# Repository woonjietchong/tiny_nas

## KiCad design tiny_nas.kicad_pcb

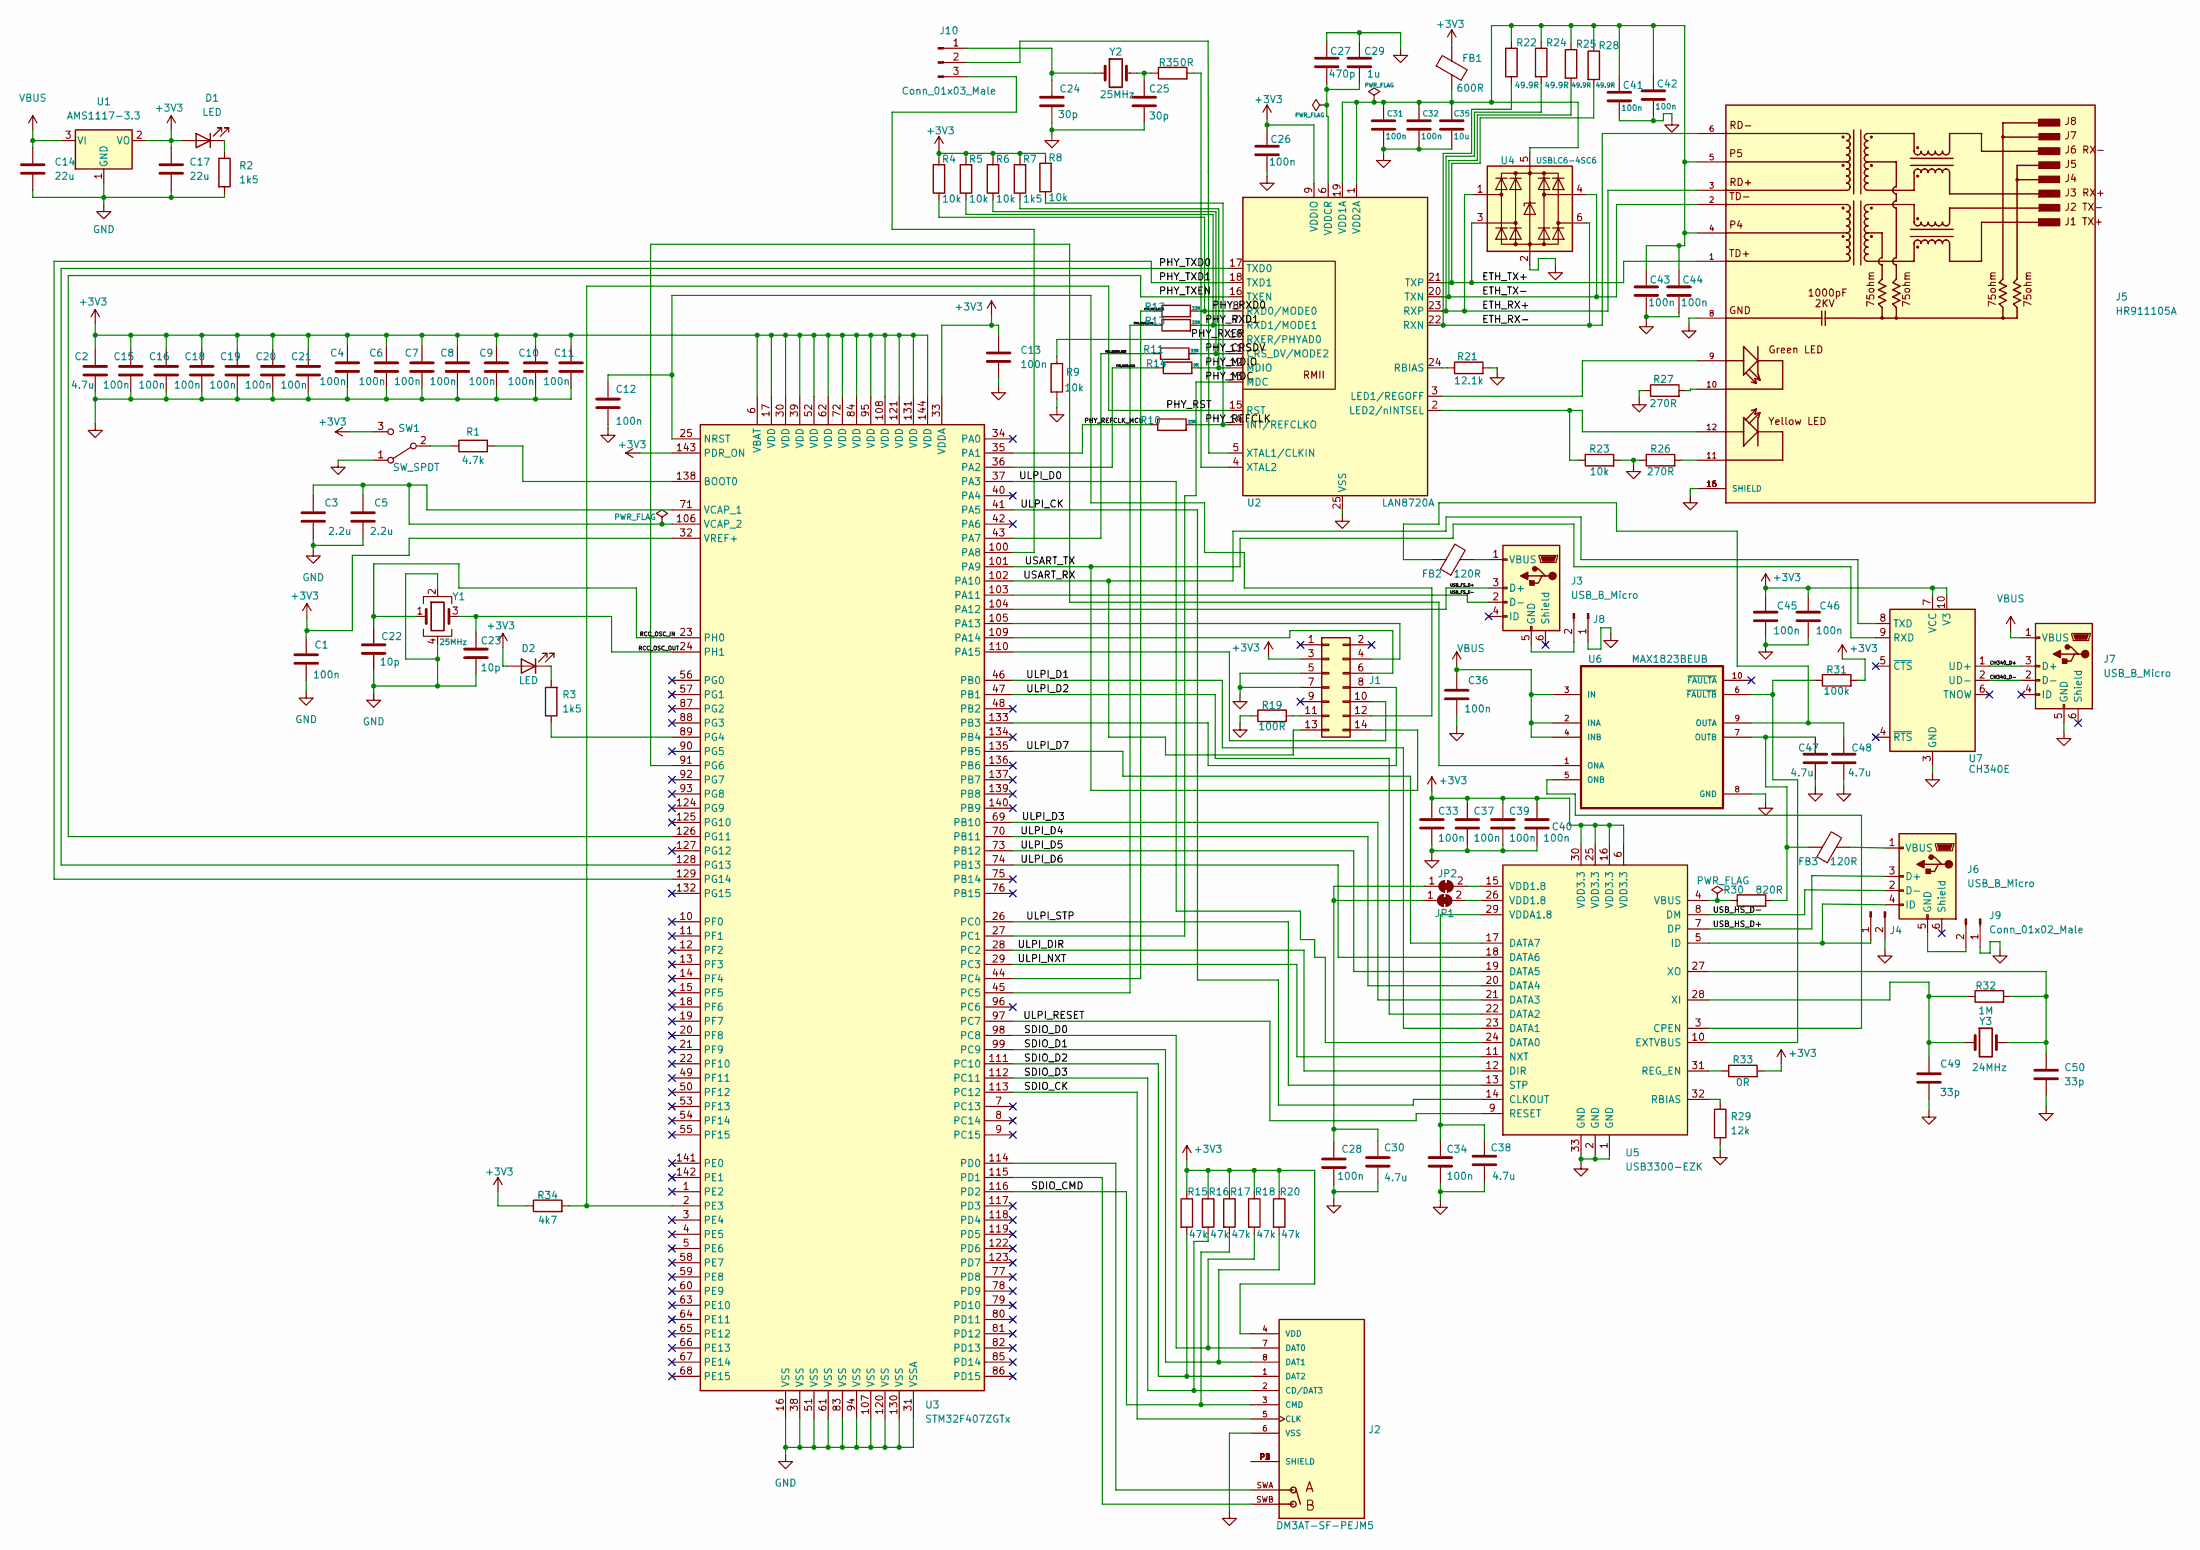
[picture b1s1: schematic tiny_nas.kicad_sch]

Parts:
C1, C4, C6, C7, C8, C9, C10, C11, C12, C13, C15, C16, C18, C19, C20, C21, C26, C28, C31, C32, C33, C34, C36, C37, C39, C40, C41, C42, C43, C44, C45, C46: 100n; C_0402_1005Metric
C2, C30, C38, C47, C48: 4.7u; C_0603_1608Metric
C3, C5: 2.2u; C_0603_1608Metric
C14, C17: 22u; C_0805_2012Metric
C22, C23: 10p; C_0402_1005Metric
C24, C25: 30p; C_0402_1005Metric
C27: 470p; C_0402_1005Metric
C29: 1u; C_0603_1608Metric
C35: 10u; C_0805_2012Metric
C49, C50: 33p; C_0402_1005Metric
D1, D2: LED; LED_0603_1608Metric
FB1: 600R; L_0603_1608Metric
FB2, FB3: 120R; L_0603_1608Metric
J1: Conn_02x07_Odd_Even; PinHeader_2x07_P1.27mm_Vertical
J2: DM3AT-SF-PEJM5; HRS_DM3AT-SF-PEJM5
J3, J6, J7: USB_B_Micro; USB_Micro-B_Molex_47346-0001
J4, J8, J9: Conn_01x02_Male; PinHeader_1x02_P2.54mm_Vertical
J5: HR911105A; HANRUN_HR911105A; PARTREV A
J10: Conn_01x03_Male; PinHeader_1x03_P2.54mm_Vertical
JP1, JP2: SolderJumper_2_Bridged; SolderJumper-2_P1.3mm_Bridged_RoundedPad1.0x1.5mm
R1: 4.7k; R_0402_1005Metric
R2, R3, R7: 1k5; R_0402_1005Metric
R4, R5, R6, R8, R9, R23: 10k; R_0402_1005Metric
R10, R11, R12, R13: 33R; R_0402_1005Metric
R14, R33, R35: 0R; R_0603_1608Metric
R15, R16, R17, R18, R20: 47k; R_0402_1005Metric
R19: 100R; R_0402_1005Metric
R21: 12.1k; R_0402_1005Metric
R22, R24, R25, R28: 49.9R; R_0805_2012Metric
R26, R27: 270R; R_0603_1608Metric
R29: 12k; R_0402_1005Metric
R30: 820R; R_0603_1608Metric
R31: 100k; R_0402_1005Metric
R32: 1M; R_0402_1005Metric
R34: 4k7; R_0402_1005Metric
SW1: SW_SPDT; SW_SPDT_PCM12
U1: AMS1117-3.3; SOT-223-3_TabPin2
U2: LAN8720A; QFN-24-1EP_4x4mm_P0.5mm_EP2.6x2.6mm
U3: STM32F407ZGTx; LQFP-144_20x20mm_P0.5mm
U4: USBLC6-4SC6; SOT-23-6
U5: USB3300-EZK; QFN-32-1EP_5x5mm_P0.5mm_EP3.45x3.45mm
U6: MAX1823BEUB; SOP50P490X110-10N
U7: CH340E; MSOP-10_3x3mm_P0.5mm
Y1: 25MHz; Crystal_SMD_3225-4Pin_3.2x2.5mm
Y2: 25MHz; Crystal_HC49-U_Vertical
Y3: 24MHz; Crystal_HC49-U_Vertical

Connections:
+3V3: C1.1, C2.1, C4.1, C6.1, C7.1, C8.1, C9.1, C10.1, C11.1, C13.1, C15.1, C16.1, C17.1, C18.1, C19.1, C20.1, C21.1, C26.1, C33.1, C37.1, C39.1, C40.1, C45.1, C46.1, D1.2 (A), D2.2 (A), FB1.1, J1.3, J2.4 (VDD), R4.2, R5.2, R6.2, R7.2, R8.2, R15.1, R16.1, R17.1, R18.1, R20.1, R31.2, R33.2, R34.1, SW1.3 (C), U1.2 (VO), U2.9 (VDDIO), U3.6 (VBAT), U3.17 (VDD), U3.30 (VDD), U3.32 (VREF+), U3.33 (VDDA), U3.39 (VDD), U3.52 (VDD), U3.62 (VDD), U3.72 (VDD), U3.84 (VDD), U3.95 (VDD), U3.108 (VDD), U3.121 (VDD), U3.131 (VDD), U3.143 (PDR_ON), U3.144 (VDD), U5.6 (VDD3.3), U5.16 (VDD3.3), U5.25 (VDD3.3), U5.30 (VDD3.3), U7.7 (VCC), U7.10 (V3)
/CH340_D+: J7.3 (D+), U7.1 (UD+)
/CH340_D-: J7.2 (D-), U7.2 (UD-)
/ETH_RX+: J5.3, R24.2, U2.23 (RXP), U4.1 (I/O1)
/ETH_RX-: J5.6, R22.2, U2.22 (RXN), U4.6 (I/O4)
/ETH_TX+: J5.1, R28.2, U2.21 (TXP), U4.3 (I/O2)
/ETH_TX-: J5.2, R25.2, U2.20 (TXN), U4.4 (I/O3)
/PHY_CRSDV: R6.1, R11.2, U2.11 (CRS_DV/MODE2)
/PHY_CRSDV_MCU: R11.1, U3.43 (PA7)
/PHY_MDC: U2.13 (MDC), U3.27 (PC1)
/PHY_MDIO: R7.1, R14.2, U2.12 (MDIO)
/PHY_MDIO_MCU: R14.1, U3.36 (PA2)
/PHY_REFCLK: R8.1, R10.2, U2.14 (INT/REFCLKO)
/PHY_REFCLK_MCU: R10.1, U3.35 (PA1)
/PHY_RST: R34.2, U2.15 (RST), U3.2 (PE3)
/PHY_RXD0: R4.1, R12.2, U2.8 (RXD0/MODE0)
/PHY_RXD0_MCU: R12.1, U3.44 (PC4)
/PHY_RXD1: R5.1, R13.2, U2.7 (RXD1/MODE1)
/PHY_RXD1_MCU: R13.1, U3.45 (PC5)
/PHY_RXER: R9.1, U2.10 (RXER/PHYAD0)
/PHY_TXD0: U2.17 (TXD0), U3.128 (PG13)
/PHY_TXD1: U2.18 (TXD1), U3.129 (PG14)
/PHY_TXEN: U2.16 (TXEN), U3.126 (PG11)
/RCC_OSC_IN: C22.1, U3.23 (PH0), Y1.1
/RCC_OSC_OUT: C23.1, U3.24 (PH1), Y1.3
/SDIO_CK: J2.5 (CLK), U3.113 (PC12)
/SDIO_CMD: J2.3 (CMD), R17.2, U3.116 (PD2)
/SDIO_D0: J2.7 (DAT0), R18.2, U3.98 (PC8)
/SDIO_D1: J2.8 (DAT1), R20.2, U3.99 (PC9)
/SDIO_D2: J2.1 (DAT2), R15.2, U3.111 (PC10)
/SDIO_D3: J2.2 (CD/DAT3), R16.2, U3.112 (PC11)
/ULPI_CK: U3.41 (PA5), U5.14 (CLKOUT)
/ULPI_D0: U3.37 (PA3), U5.24 (DATA0)
/ULPI_D1: U3.46 (PB0), U5.23 (DATA1)
/ULPI_D2: U3.47 (PB1), U5.22 (DATA2)
/ULPI_D3: U3.69 (PB10), U5.21 (DATA3)
/ULPI_D4: U3.70 (PB11), U5.20 (DATA4)
/ULPI_D5: U3.73 (PB12), U5.19 (DATA5)
/ULPI_D6: U3.74 (PB13), U5.18 (DATA6)
/ULPI_D7: U3.135 (PB5), U5.17 (DATA7)
/ULPI_DIR: U3.28 (PC2), U5.12 (DIR)
/ULPI_NXT: U3.29 (PC3), U5.11 (NXT)
/ULPI_RESET: U3.97 (PC7), U5.9 (RESET)
/ULPI_STP: U3.26 (PC0), U5.13 (STP)
/USART_RX: J1.13, U3.102 (PA10), U7.8 (TXD)
/USART_TX: J1.14, U3.101 (PA9), U7.9 (RXD)
/USB_FS_D+: J3.3 (D+), U3.104 (PA12)
/USB_FS_D-: J3.2 (D-), U3.103 (PA11)
/USB_HS_D+: J6.3 (D+), U5.7 (DP)
/USB_HS_D-: J6.2 (D-), U5.8 (DM)
GND: C1.2, C2.2, C3.2, C4.2, C5.2, C6.2, C7.2, C8.2, C9.2, C10.2, C11.2, C12.1, C13.2, C14.2, C15.2, C16.2, C17.2, C18.2, C19.2, C20.2, C21.2, C22.2, C23.2, C24.2, C25.2, C26.2, C27.1, C28.2, C29.1, C30.2, C31.2, C32.2, C33.2, C34.2, C35.2, C36.2, C37.2, C38.2, C39.2, C40.2, C41.2, C42.2, C43.2, C44.2, C45.2, C46.2, C47.2, C48.2, C49.2, C50.2, J1.5, J1.7, J2.6 (VSS), J4.2, J5.8, J5.15 (SHIELD), J5.16 (SHIELD), J7.5 (GND), J8.1, J9.1, R2.2, R9.2, R19.1, R21.2, R23.2, R26.1, R27.1, R29.2, SW1.1 (A), U1.1 (GND), U2.25 (VSS), U3.16 (VSS), U3.31 (VSSA), U3.38 (VSS), U3.51 (VSS), U3.61 (VSS), U3.83 (VSS), U3.94 (VSS), U3.107 (VSS), U3.120 (VSS), U3.130 (VSS), U4.2 (GND), U5.1 (GND), U5.2 (GND), U5.33 (GND), U6.8 (GND), U7.3 (GND), Y1.2, Y1.4
unnamed: C3.1, C5.1, U3.71 (VCAP_1), U3.106 (VCAP_2)
unnamed: C12.2, J1.12, U3.25 (NRST)
unnamed: C24.1, J10.1, Y2.1
unnamed: C25.1, R35.1, Y2.2
unnamed: C27.2, C29.2, U2.6 (VDDCR)
unnamed: C28.1, C30.1, JP1.1 (A), JP2.1 (A)
unnamed: C31.1, C32.1, C35.1, C41.1, C42.1, C43.1, C44.1, FB1.2, J5.4, J5.5, R22.1, R24.1, R25.1, R28.1, U2.1 (VDD2A), U2.19 (VDD1A), U4.5 (VBUS)
unnamed: C34.1, C38.1, U5.29 (VDDA1.8)
unnamed: C47.1, FB3.1, R30.2, U6.7 (OUTB)
unnamed: C48.1, FB2.1, U6.9 (OUTA)
unnamed: C49.1, R32.1, U5.28 (XI), Y3.1
unnamed: C50.1, R32.2, U5.27 (XO), Y3.2
unnamed: D1.1 (K), R2.1
unnamed: D2.1 (K), R3.2
unnamed: FB2.2, J3.1 (VBUS)
unnamed: FB3.2, J6.1 (VBUS)
unnamed: J1.4, U3.105 (PA13)
unnamed: J1.6, U3.109 (PA14)
unnamed: J1.8, U3.133 (PB3)
unnamed: J1.10, U3.110 (PA15)
unnamed: J1.11, R19.2
unnamed: J2.P1 (SHIELD), J2.P2 (SHIELD), J2.P3 (SHIELD), J2.P4 (SHIELD)
unnamed: J2.SWA, U3.114 (PD0)
unnamed: J2.SWB, U3.115 (PD1)
unnamed: J3.5 (GND), J8.2
unnamed: J4.1, J6.4 (ID), U5.5 (ID)
unnamed: J5.9, U2.3 (LED1/REGOFF)
unnamed: J5.10, R27.2
unnamed: J5.11, R26.2
unnamed: J5.12, R23.1, U2.2 (LED2/nINTSEL)
unnamed: J6.5 (GND), J9.2
unnamed: J10.2, U2.5 (XTAL1/CLKIN)
unnamed: J10.3, U3.100 (PA8)
unnamed: JP1.2 (B), U5.26 (VDD1.8)
unnamed: JP2.2 (B), U5.15 (VDD1.8)
unnamed: R1.1, SW1.2 (B)
unnamed: R1.2, U3.138 (BOOT0)
unnamed: R3.1, U3.89 (PG4)
unnamed: R21.1, U2.24 (RBIAS)
unnamed: R29.1, U5.32 (RBIAS)
unnamed: R30.1, U5.4 (VBUS)
unnamed: R31.1, U5.10 (EXTVBUS), U6.6 (~FAULTB)
unnamed: R33.1, U5.31 (REG_EN)
unnamed: R35.2, U2.4 (XTAL2)
unnamed: U3.91 (PG6), U6.1 (ONA)
unnamed: U5.3 (CPEN), U6.5 (ONB)
VBUS: C14.1, C36.1, J7.1 (VBUS), U1.3 (VI), U6.2 (INA), U6.3 (IN), U6.4 (INB)

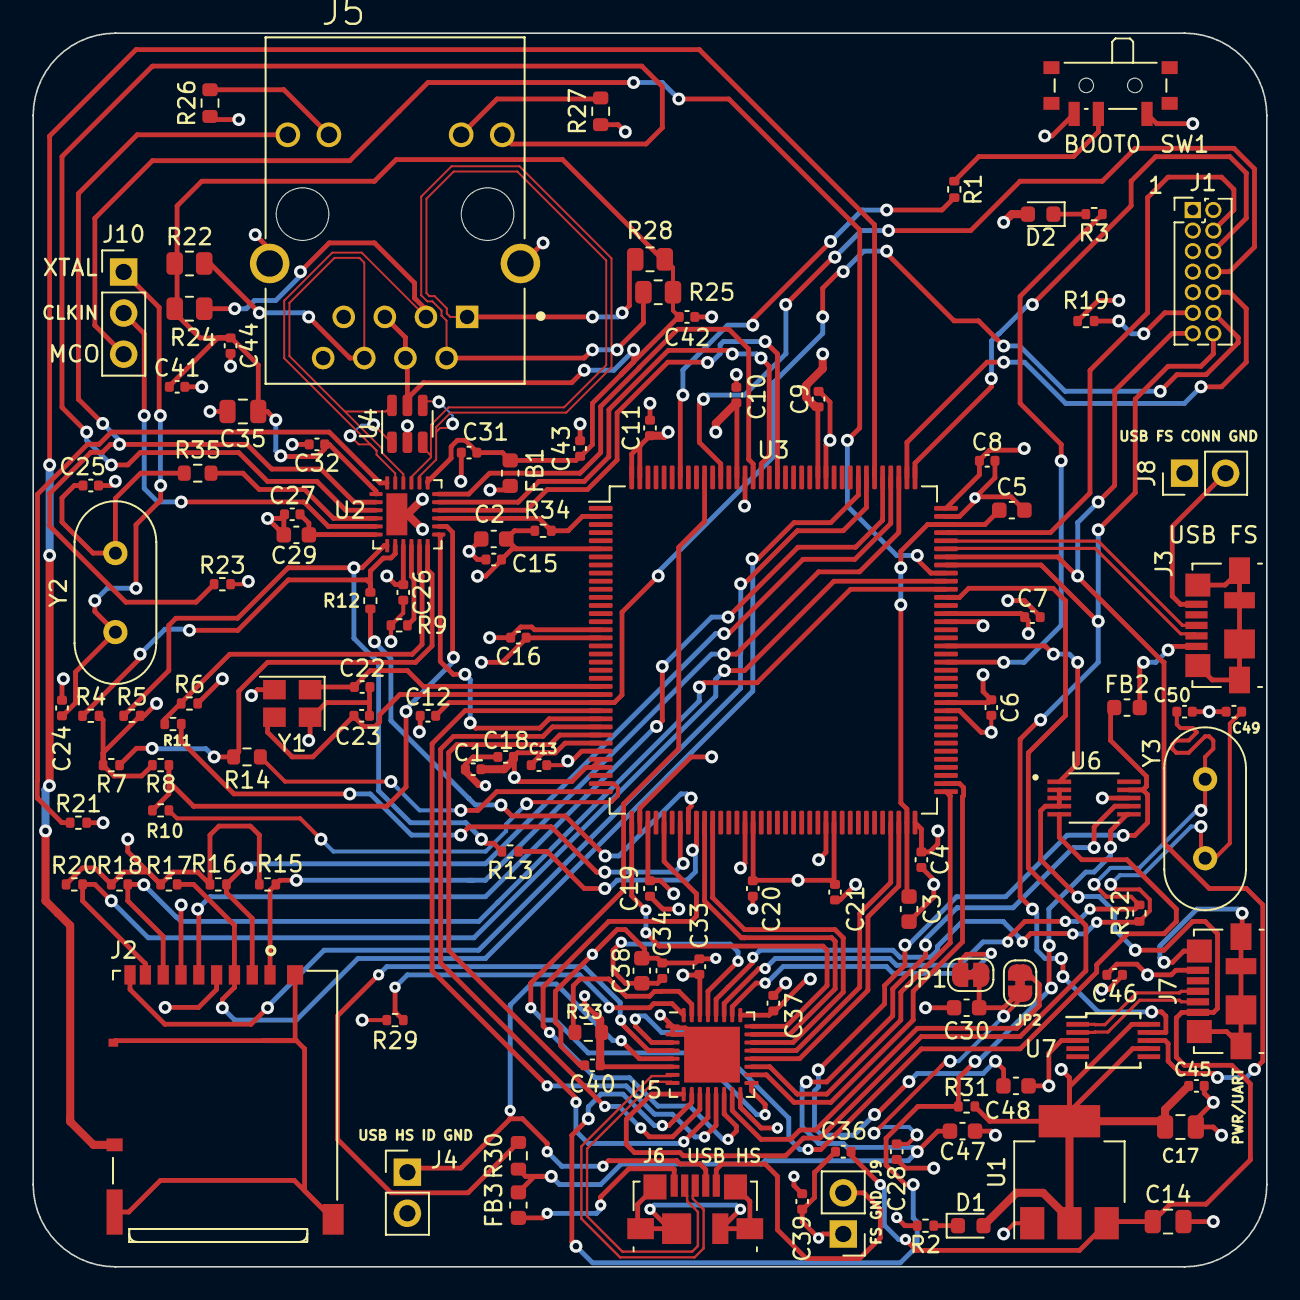
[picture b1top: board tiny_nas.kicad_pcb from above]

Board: 4 copper layers, 76.2 x 76.2 mm, 113 parts (0 on the bottom side), 98 nets.

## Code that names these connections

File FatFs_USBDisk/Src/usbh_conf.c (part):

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	__HAL_RCC_GPIOA_CLK_ENABLE();
	__HAL_RCC_GPIOB_CLK_ENABLE();
	/**USB_OTG_HS GPIO Configuration
	PC0     ------> USB_OTG_HS_ULPI_STP
	PC2     ------> USB_OTG_HS_ULPI_DIR
	PC3     ------> USB_OTG_HS_ULPI_NXT
	PA3     ------> USB_OTG_HS_ULPI_D0
	PA5     ------> USB_OTG_HS_ULPI_CK
	PB0     ------> USB_OTG_HS_ULPI_D1
	PB1     ------> USB_OTG_HS_ULPI_D2
	PB10     ------> USB_OTG_HS_ULPI_D3
	PB11     ------> USB_OTG_HS_ULPI_D4
	PB12     ------> USB_OTG_HS_ULPI_D5
	PB13     ------> USB_OTG_HS_ULPI_D6
	PB5     ------> USB_OTG_HS_ULPI_D7
	*/
	GPIO_InitStruct.Pin = GPIO_PIN_0|GPIO_PIN_2|GPIO_PIN_3;
	GPIO_InitStruct.Mode = GPIO_MODE_AF_PP;
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
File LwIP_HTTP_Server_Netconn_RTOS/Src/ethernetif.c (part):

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  __HAL_RCC_GPIOA_CLK_ENABLE();
  __HAL_RCC_GPIOG_CLK_ENABLE();
  /**ETH GPIO Configuration
  PC1     ------> ETH_MDC
  PA1     ------> ETH_REF_CLK
  PA2     ------> ETH_MDIO
  PA7     ------> ETH_CRS_DV
  PC4     ------> ETH_RXD0
  PC5     ------> ETH_RXD1
  PG11     ------> ETH_TX_EN
  PG13     ------> ETH_TXD0
  PG14     ------> ETH_TXD1
  */
  GPIO_InitStruct.Pin = GPIO_PIN_1|GPIO_PIN_4|GPIO_PIN_5;
  GPIO_InitStruct.Mode = GPIO_MODE_AF_PP;
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
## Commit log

2022-08-08 complete first draft of schematics
2022-08-08 pcb component placement
2022-08-09 route USB3300
2022-08-09 route all
2022-08-09 passed DRC
2022-08-14 Added Ethernet PHY reset GPIO and pin header to choose input clock from MCO or crystal
2022-08-27 change resistors footprint, add manufacturing files
2022-08-27 change bom
2022-09-11 initial fw 11 sep 2022
2022-09-11 usb and sd card fw

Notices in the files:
FatFs_USBDisk/Src/usbh_conf.c:
Copyright (c) 2017 STMicroelectronics.
All rights reserved.
This software is licensed under terms that can be found in the LICENSE file
